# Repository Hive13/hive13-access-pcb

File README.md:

# hive13-access-pcb
KiCad files for the circuit board that controls doors.

## Board Design
This board is designed so that it can be sent to a fab house and done dual-layer, or milled with a CNC, single-sided, and done in the "jumper links" style.
This results in several constraints:
- The top-side PCB traces need to both be in a straight line and not cross over any top-side components.
- All surface-mount components need to be on the bottom layer.
- No vias under bottom-side components.
- Assume that there will be no bottom-side solder mask.  Take this into account when running traces under a bottom-side component.

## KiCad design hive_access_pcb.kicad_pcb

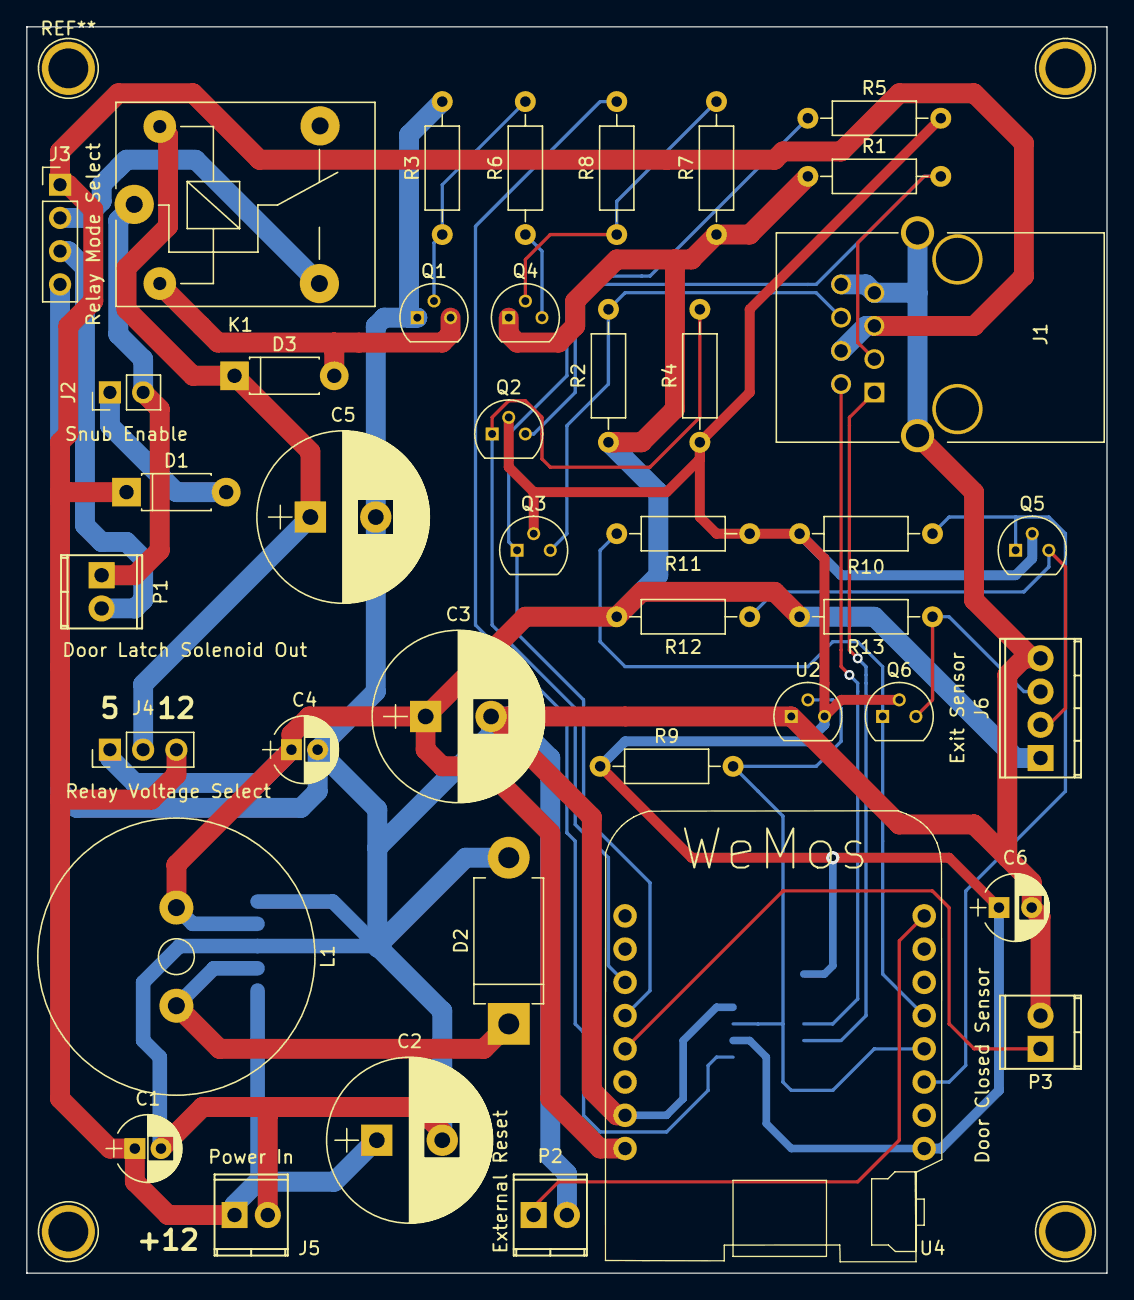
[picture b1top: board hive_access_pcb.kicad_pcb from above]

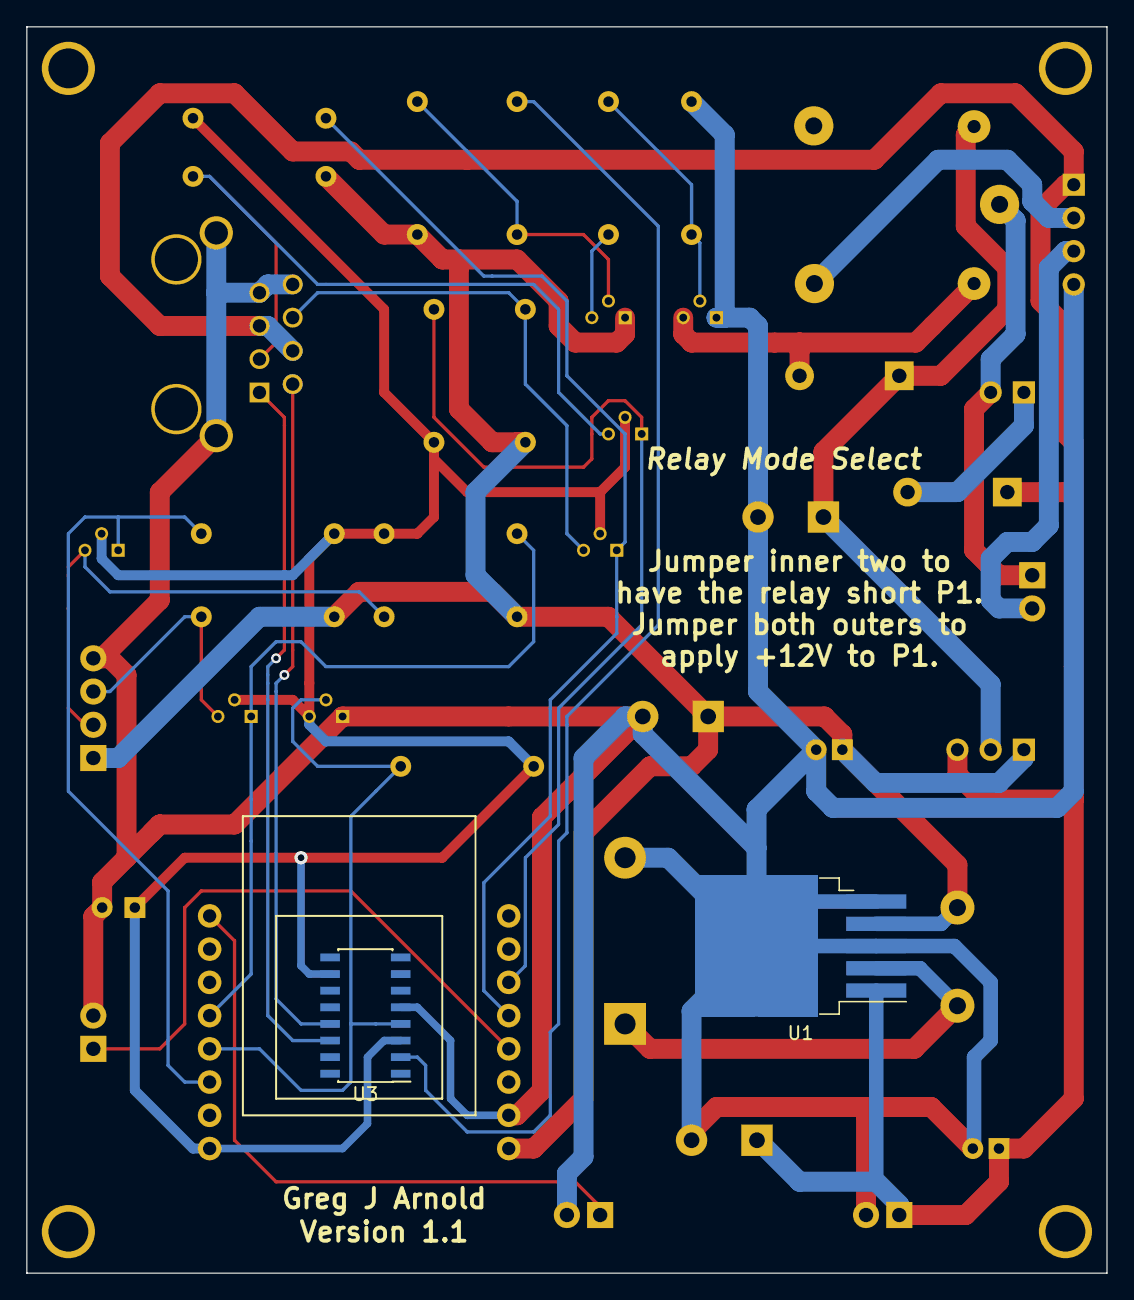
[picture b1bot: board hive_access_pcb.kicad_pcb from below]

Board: 2 copper layers, 82.6 x 95.2 mm, 43 parts (2 on the bottom side), 28 nets.

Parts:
C1, C4: 1MFD; CP_Radial_D5.0mm_P2.00mm
C2: 100MFD; CP_Radial_D12.5mm_P5.00mm
C3, C5: 1000MFD; CP_Radial_D13.0mm_P5.00mm
C6: 1MFD; CP_Radial_D5.0mm_P2.50mm
D1, D3: 1N4002; D_DO-41_SOD81_P7.62mm_Horizontal
D2: D_Schottky; D_DO-201AD_P12.70mm_Horizontal
J1: Door Reader; RJ45_SHIELD
J2: Snub Enable; Pin_Header_Straight_1x02_Pitch2.54mm
J3: Relay Mode Select; Pin_Header_Straight_1x04_Pitch2.54mm
J4: Relay Voltage Select; Pin_Header_Straight_1x03_Pitch2.54mm
J5: Power In; TerminalBlock_Pheonix_MPT-2.54mm_2pol
J6: Exit Sensor; TerminalBlock_Pheonix_MPT-2.54mm_4pol
K1: SANYOU_SRD_Form_C; Relay_SPDT_SANYOU_SRD_Series_Form_C
L1: L; L_Radial_D21.0mm_P7.5mm
P1: Door Latch Solenoid Out; TerminalBlock_Pheonix_MPT-2.54mm_2pol
P2: External Reset; TerminalBlock_Pheonix_MPT-2.54mm_2pol
P3: Door Closed Sensor; TerminalBlock_Pheonix_MPT-2.54mm_2pol
Q1: 2N2222; TO-92_Molded_Narrow
Q2, Q3, Q5, Q6: 2N7000; TO-92_Molded_Narrow
Q4: 2N3906; TO-92_Molded_Narrow
R1, R2, R3, R4, R5, R7, R10, R11, R12, R13: 10kΩ; R_Axial_DIN0207_L6.3mm_D2.5mm_P10.16mm_Horizontal
R6: 1.2kΩ; R_Axial_DIN0207_L6.3mm_D2.5mm_P10.16mm_Horizontal
R8: 1kΩ; R_Axial_DIN0207_L6.3mm_D2.5mm_P10.16mm_Horizontal
R9: 4.7kΩ; R_Axial_DIN0207_L6.3mm_D2.5mm_P10.16mm_Horizontal
U1: LM2576S-5; TO-263-5_TabPin3
U2: DS18B20; TO-92_Molded_Narrow
U3: DS2408; SOIC-16_3.9x9.9mm_Pitch1.27mm
U4: WeMos_mini; D1_mini_board

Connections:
+3V3: C6.1, Q2.2, Q3.2, Q5.2, Q6.2, R4.1, R5.2, R9.1, R10.2, R11.1, U2.3, U3.3, U3.10, U4.16
+5V: C3.1, C4.1, J4.1, J6.1, L1.1, Q4.1, R1.1, R2.1, R7.1, R12.2, R13.2, U1.4, U4.1
+12V: C1.1, C2.1, D1.1, J1.4, J1.5, J3.1, J4.3, J5.1, U1.1
/BASE_DOOR: Q1.2, R3.1, R6.2
/BASE_DOOR_2: Q4.2, R7.2, R8.1
/CONN_CONTACT: J3.3, P1.2
/DOOR_OPEN: R8.2, U3.2
/DOOR_SENSOR: P3.1, U4.4
/HC_ECHO: J6.3, Q6.3, R13.1
/HC_TRIG: J6.2, Q5.3, R12.1
/ONE_WIRE: R9.2, U2.2, U3.4, U4.13
/RELAY_CONN: J2.2, K1.1, P1.1
/RELAY_CONTACT: J3.2, K1.3
/RELAY_DOOR: D3.2, K1.2, Q1.3
/RELAY_POWER: C5.1, D3.1, J4.2, K1.5
/VREG_OUT: D2.1, L1.2, U1.2
/WEMOS_D0: Q3.1, R5.1, U4.5
/WEMOS_D1: Q2.1, R4.2, U4.6
/WEMOS_ECHO: Q6.1, R11.2, U4.12
/WEMOS_TRIG: Q5.1, R10.1, U4.14
/WIEGAND_BEEP: J1.1, U3.14
/WIEGAND_D0: J1.6, Q3.3, R2.2
/WIEGAND_D1: J1.3, Q2.3, R1.2
/WIEGAND_LIGHT: J1.2, U3.13
/~RST: P2.1, U4.9
GND: C1.2, C2.2, C3.2, C4.2, C5.2, C6.2, D2.2, J1.7, J1.8, J1.9, J3.4, J5.2, J6.4, P2.2, P3.2, Q1.1, R3.2, U1.3, U1.5, U2.1, U3.5, U4.2
unnamed: D1.2, J2.1
unnamed: Q4.3, R6.1

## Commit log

2018-05-26 Update README.md
    Add in design style of the board.
2018-05-26 First check-in of schematic.
2018-05-26 First draft of the schematic.
2018-05-27 Assigned all components to provisional footprints, started organizing PCB layout.
2018-05-27 All components correctly sized, except connectors. Need to check TO-92 pinouts.
2018-05-28 First draft of the circuit board.
2018-05-28 Design rule tweaks.
2018-05-28 Rename the single-sided board.
2018-05-28 Grouping components for 2-sided.
2018-05-28 Basic layout.
2018-05-28 First draft of actual PCB.
2018-06-06 Add in WeMos submodule.
2018-06-06 Fix issues.
